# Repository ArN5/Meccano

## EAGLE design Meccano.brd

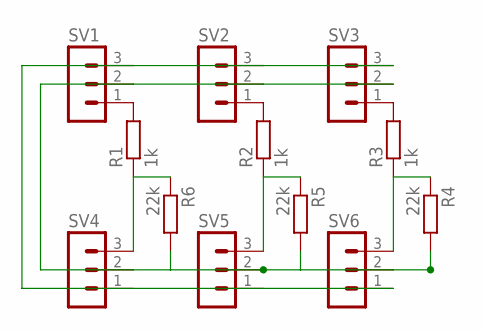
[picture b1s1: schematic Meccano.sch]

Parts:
R1, R2, R3: 1k; 0204/7
R4, R5, R6: 22k; 0204/7
SV1, SV2, SV3, SV4, SV5, SV6: MA03-1

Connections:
5V: R4.2, R5.2, R6.2, SV1.2, SV2.2, SV3.2, SV4.2, SV5.2, SV6.2
GND: SV1.3, SV2.3, SV3.3, SV4.1, SV5.1, SV6.1
unnamed: R1.2, SV1.1
unnamed: R2.2, SV2.1
unnamed: R3.2, SV3.1
unnamed: R3.1, R4.1, SV6.3
unnamed: R2.1, R5.1, SV5.3
unnamed: R1.1, R6.1, SV4.3

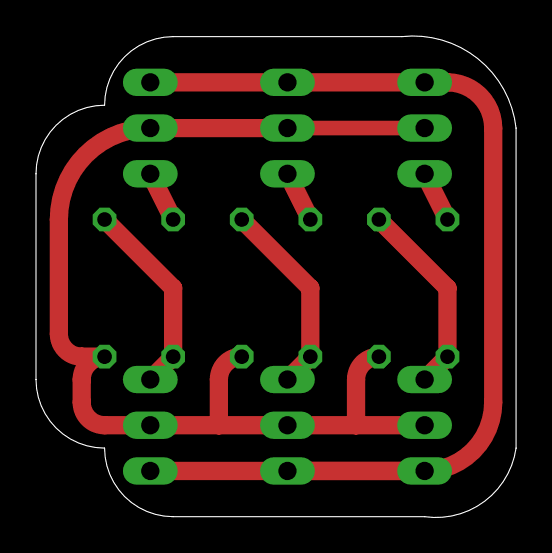
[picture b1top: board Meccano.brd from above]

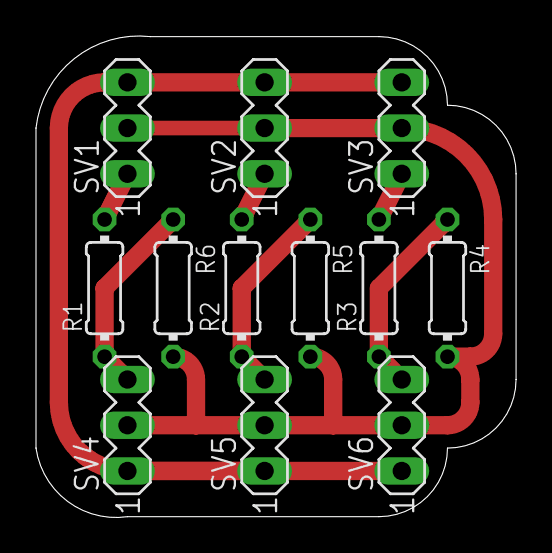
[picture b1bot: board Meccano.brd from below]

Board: 2 copper layers, 26.7 x 26.7 mm, 12 parts (12 on the bottom side), 8 nets.

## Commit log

2016-12-13 MeccanoArduinoAdapter
    This board basically allows one to control the smart modules using an
    arduino.
